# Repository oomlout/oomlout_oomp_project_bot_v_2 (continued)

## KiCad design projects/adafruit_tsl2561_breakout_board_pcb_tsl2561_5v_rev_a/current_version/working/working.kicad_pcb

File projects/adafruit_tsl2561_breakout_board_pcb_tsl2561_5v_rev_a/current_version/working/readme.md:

# tsl2561_breakout_board_pcb
 
## summary 
* id: adafruit_tsl2561_breakout_board_pcb_tsl2561_5v_rev_a
* user: adafruit
* name: tsl2561_breakout_board_pcb
* board: tsl2561_5v_rev_a
* repo: https://github.com/adafruit/TSL2561-breakout-board-PCB

* src_file_repo_sch: 
* src_file_repo_sch_link: https://github.com/adafruit/TSL2561-breakout-board-PCB/tree/master/
* full details link: https://github.com/oomlout/oomlout_oomp_project_bot_v_2/tree/main/projects/adafruit_tsl2561_breakout_board_pcb_tsl2561_5v_rev_a/current_version/working  

## schematic  
  
[schematic (pdf)](working_schematic.pdf) 

## pcb  

[board (pdf)](working.pdf)  

## working_bom
| Id | Designator | Footprint | Quantity | Designation | Supplier and ref |  | None | 
| --- | --- | --- | --- | --- | --- | --- | --- | 
| 1 | @HOLE1,@HOLE0 |  | 2 |  |  |  | [''] | 
| 2 | U$4 | STEMMA_TSL2561_B_FRONT | 1 |  |  |  | [''] | 
| 3 | U3 | TSL2561_FN | 1 | TSL2561 |  |  | [''] | 
| 4 | U2 | SOT23-5 | 1 | MIC5225-3.3 |  |  | [''] | 
| 5 | FID2,FID1 | FIDUCIAL_1MM | 2 | FIDUCIAL_1MM |  |  | [''] | 
| 6 | SCL_PAD0,GND_PAD0,SDA_PAD0,VIN_PAD0 | SEWALLI | 4 | SEWTAP-ALLIGATOR |  |  | [''] | 
| 7 | Q3 | SOT363 | 1 | 2N7002D |  |  | [''] | 
| 8 | X1 | JSTPH4 | 1 | STEMMA_I2C_RASMT |  |  | [''] | 
| 9 | R1 | RESPACK_4X0603 | 1 | 10K |  |  | [''] | 
| 10 | C2,C1 | 0805-NO | 2 | 10uF |  |  | [''] | 
| 11 | U$8 | PCBFEAT-REV-040 | 1 |  |  |  | [''] | 
| 12 | SJ1 | SOLDERJUMPER_2WAY_OPEN_NOPASTE | 1 |  |  |  | [''] | 
| 13 | U$7 | STEMMA_TSL2561_B_BACK | 1 |  |  |  | [''] | 

## bom_schematic
| Ref | Qnty | Value | Cmp name | Footprint | Description | Vendor | DNP | 
| --- | --- | --- | --- | --- | --- | --- | --- | 
| C1, C2 | 2 | 10uF | CAP_CERAMIC0805-NOOUTLINE | working:0805-NO |  |  |  | 
| FID1, FID2 | 2 | FIDUCIAL_1MM | FIDUCIAL_1MM | working:FIDUCIAL_1MM |  |  |  | 
| GND_PAD0 | 1 | SEWTAP-ALLIGATOR | SEWTAP-ALLIGATOR | working:SEWALLI |  |  |  | 
| Q3 | 1 | 2N7002D | MOSFET-N_DUAL | working:SOT363 |  |  |  | 
| R1 | 1 | 10K | RESISTOR_4PACK | working:RESPACK_4X0603 |  |  |  | 
| SCL_PAD0 | 1 | SEWTAP-ALLIGATOR | SEWTAP-ALLIGATOR | working:SEWALLI |  |  |  | 
| SDA_PAD0 | 1 | SEWTAP-ALLIGATOR | SEWTAP-ALLIGATOR | working:SEWALLI |  |  |  | 
| SJ1 | 1 | SOLDERJUMPER_2WAY | SOLDERJUMPER_2WAY | working:SOLDERJUMPER_2WAY_OPEN_NOPASTE |  |  |  | 
| U2 | 1 | MIC5225-3.3 | VREG_SOT23-5 | working:SOT23-5 |  |  |  | 
| U3 | 1 | TSL2561 | LIGHT_TSL2561 | working:TSL2561_FN |  |  |  | 
| VIN_PAD0 | 1 | SEWTAP-ALLIGATOR | SEWTAP-ALLIGATOR | working:SEWALLI |  |  |  | 
| X1 | 1 | STEMMA_I2C_RASMT | STEMMA_I2C_RASMT | working:JSTPH4 |  |  |  |

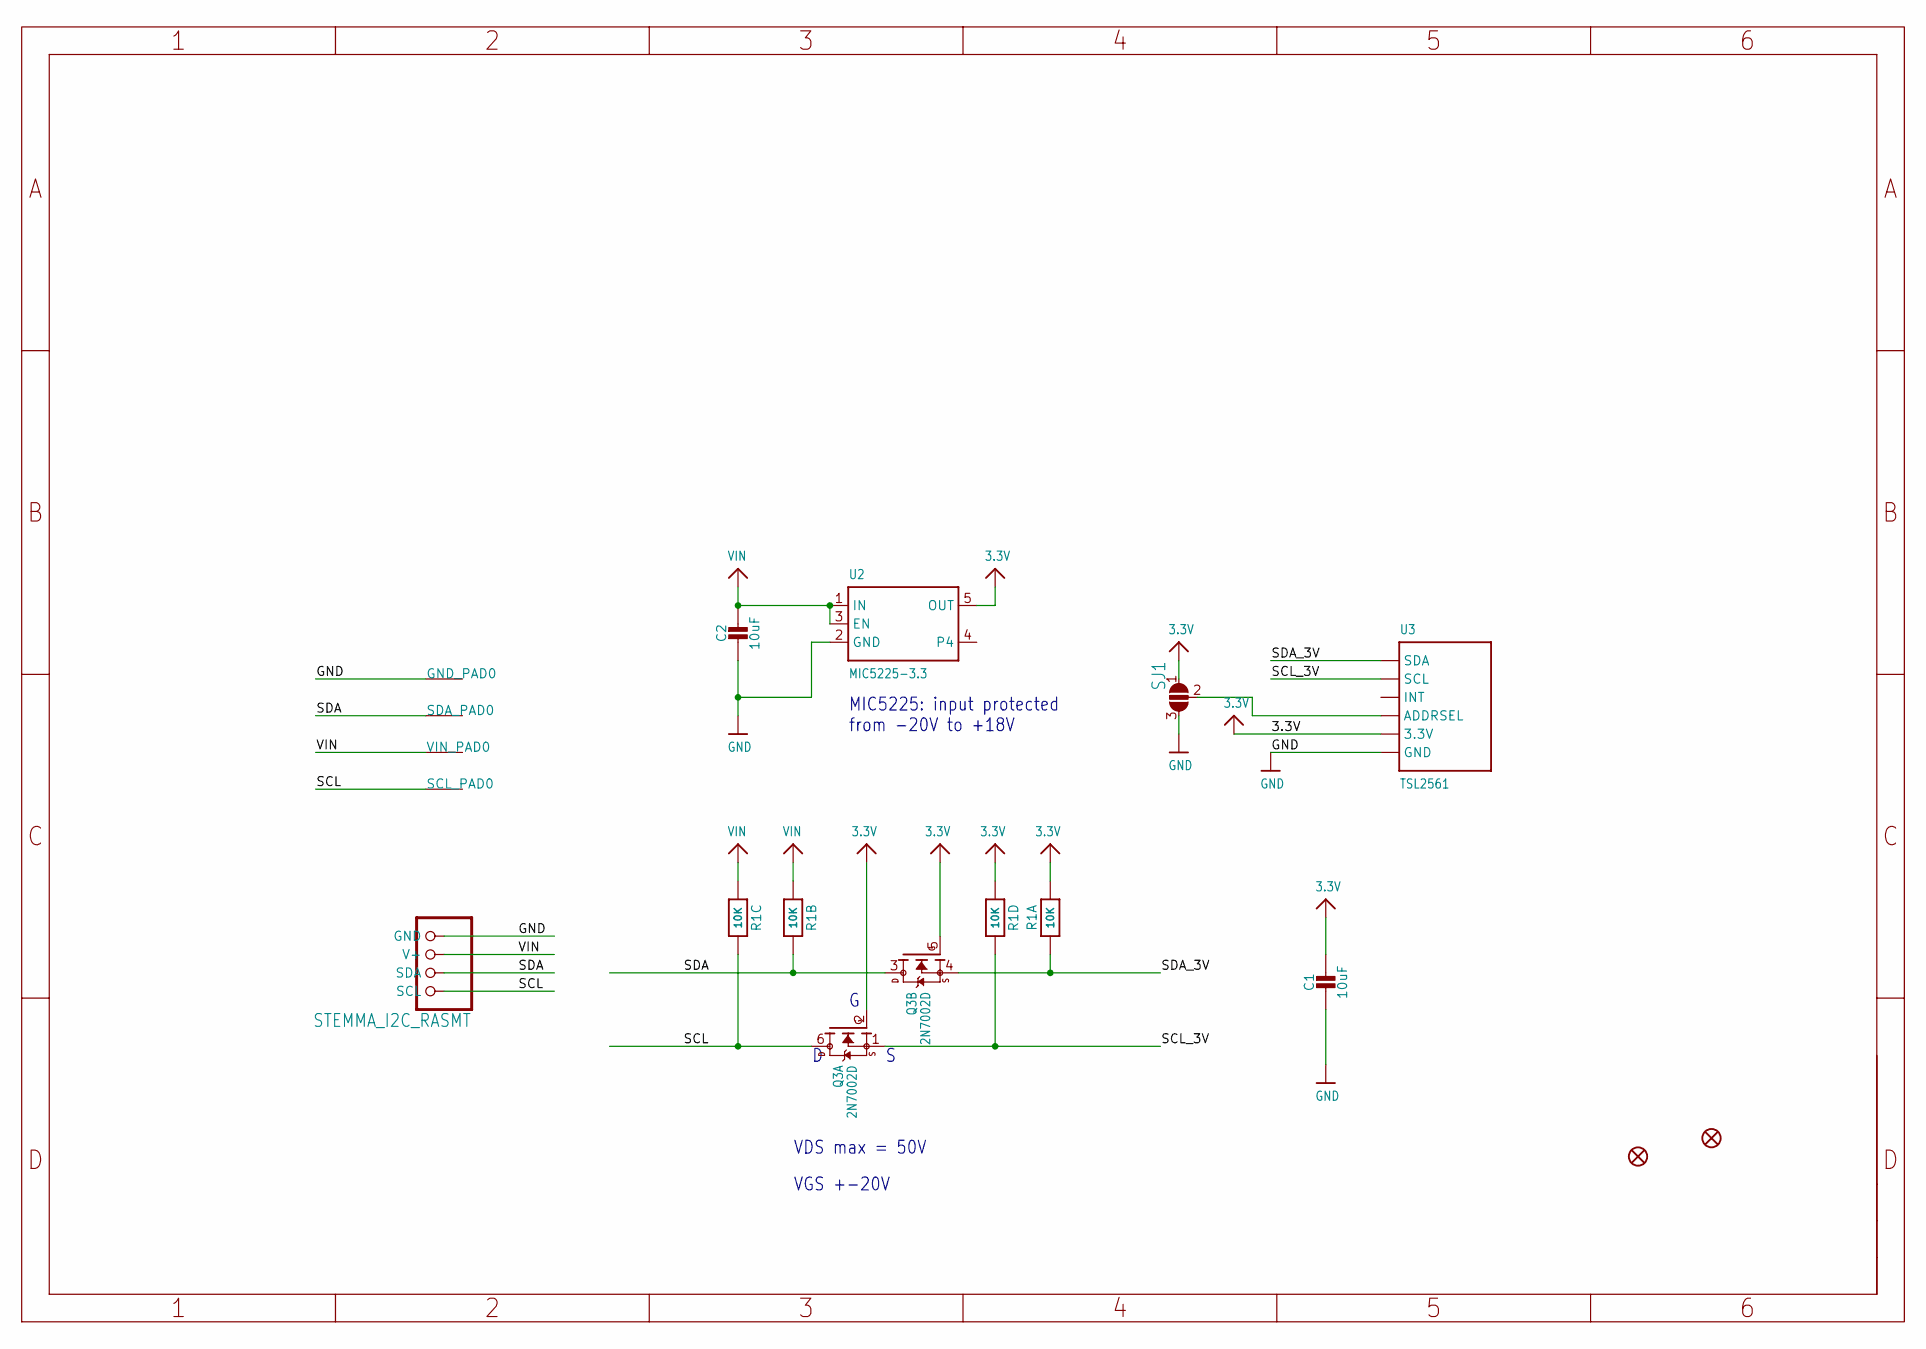
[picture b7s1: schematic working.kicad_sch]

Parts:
C1, C2: 10uF; 0805-NO
FID1, FID2: FIDUCIAL_1MM
GND_PAD0: SEWTAP-ALLIGATOR; SEWALLI
Q3: 2N7002D; SOT363
R1: 10K; RESPACK_4X0603
SCL_PAD0: SEWTAP-ALLIGATOR; SEWALLI
SDA_PAD0: SEWTAP-ALLIGATOR; SEWALLI
SJ1: SOLDERJUMPER_2WAY; SOLDERJUMPER_2WAY_OPEN_NOPASTE
U2: MIC5225-3.3; SOT23-5
U3: TSL2561; TSL2561_FN
VIN_PAD0: SEWTAP-ALLIGATOR; SEWALLI
X1: STEMMA_I2C_RASMT; JSTPH4

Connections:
3.3V: C1.1, Q3.2 (G), Q3.5 (G), R1.1, R1.5 (2), SJ1.1, U2.5 (OUT), U3.VDD (3.3V)
GND: C1.2, C2.2, GND_PAD0.P$1, SJ1.3, U2.2 (GND), U3.VSS (GND), X1.1 (GND)
unnamed: SJ1.2, U3.ADR (ADDRSEL)
SCL: Q3.6 (D), R1.6 (2), SCL_PAD0.P$1, X1.4 (SCL)
SCL_3V: Q3.1 (S), R1.4 (1), U3.CLK (SCL)
SDA: Q3.3 (D), R1.7 (2), SDA_PAD0.P$1, X1.3 (SDA)
SDA_3V: Q3.4 (S), R1.8 (2), U3.DATA (SDA)
VIN: C2.1, R1.2 (1), R1.3 (1), U2.1 (IN), U2.3 (EN), VIN_PAD0.P$1, X1.2 (V+)

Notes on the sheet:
VDS max = 50V
MIC5225: input protected from -20V to +18V
VGS +-20V

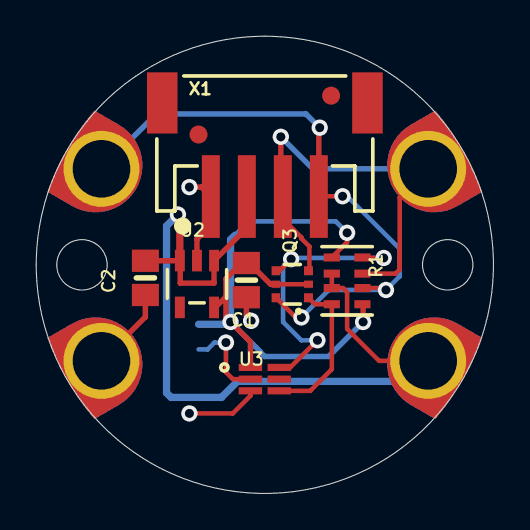
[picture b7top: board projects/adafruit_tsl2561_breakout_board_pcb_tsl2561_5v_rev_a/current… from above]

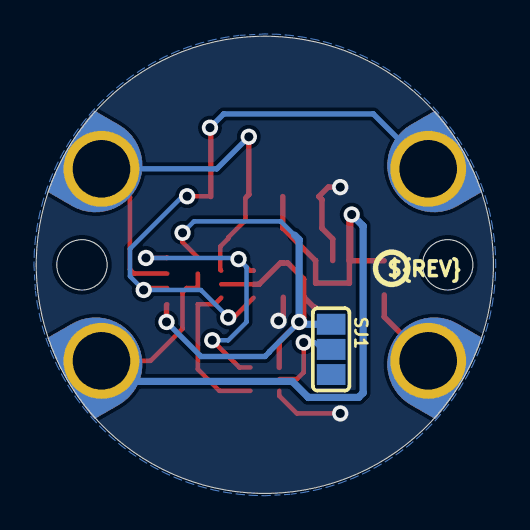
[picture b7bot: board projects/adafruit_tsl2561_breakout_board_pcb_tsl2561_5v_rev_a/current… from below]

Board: 2 copper layers, 25.4 x 25.4 mm, 19 parts (3 on the bottom side), 8 nets.

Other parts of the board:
@HOLE0, @HOLE1: (no value)
U$4: STEMMA_TSL2561_B_FRONT
U$7: STEMMA_TSL2561_B_BACK
U$8: PCBFEAT-REV-040
